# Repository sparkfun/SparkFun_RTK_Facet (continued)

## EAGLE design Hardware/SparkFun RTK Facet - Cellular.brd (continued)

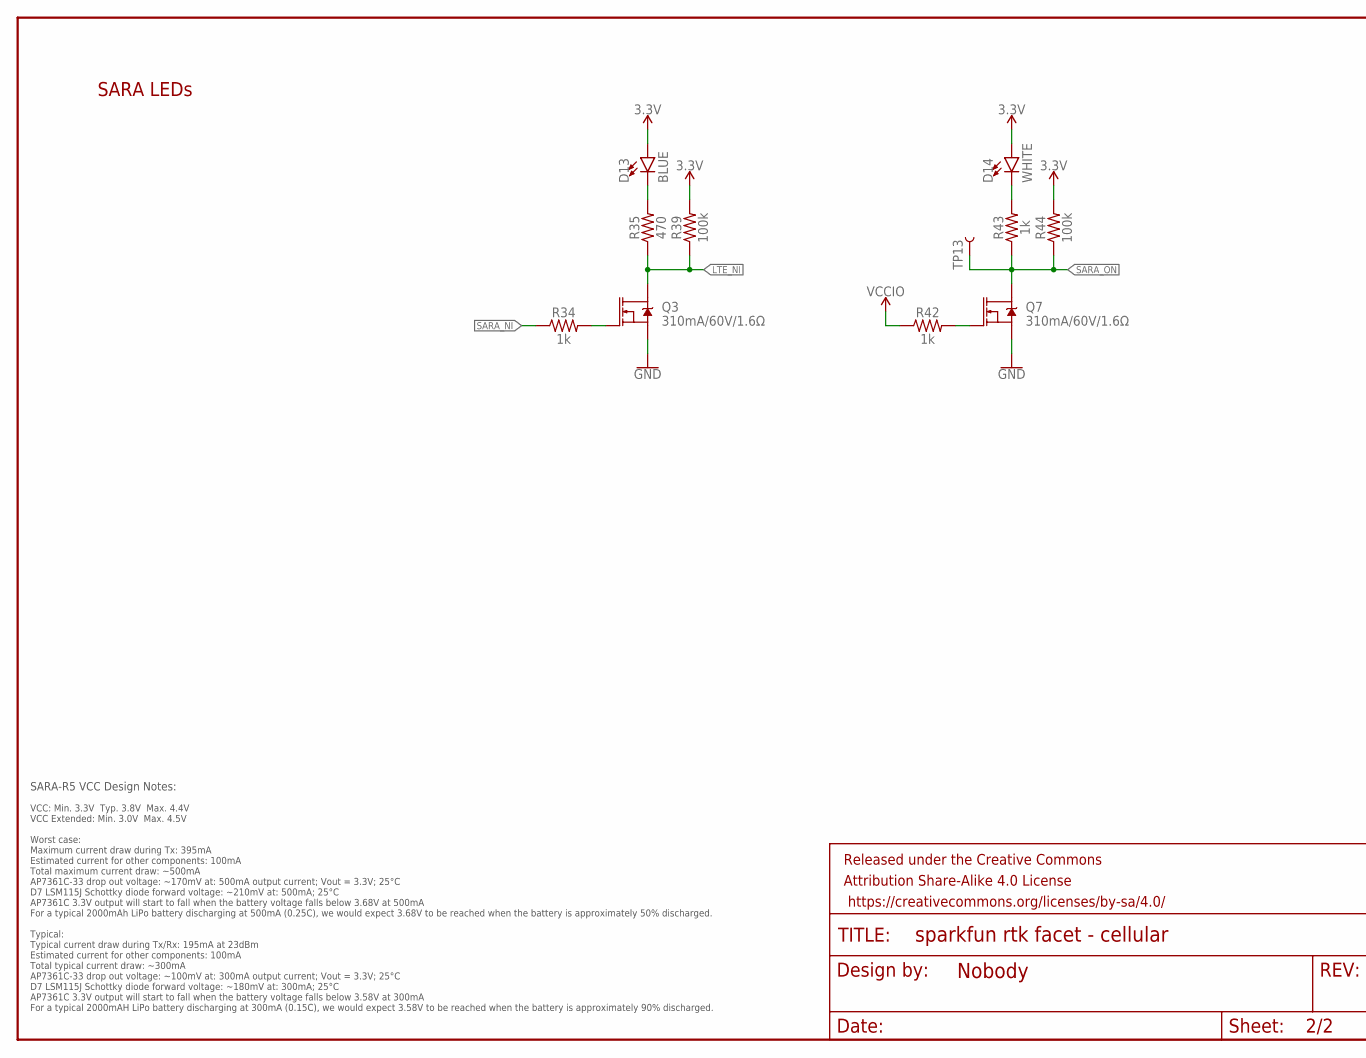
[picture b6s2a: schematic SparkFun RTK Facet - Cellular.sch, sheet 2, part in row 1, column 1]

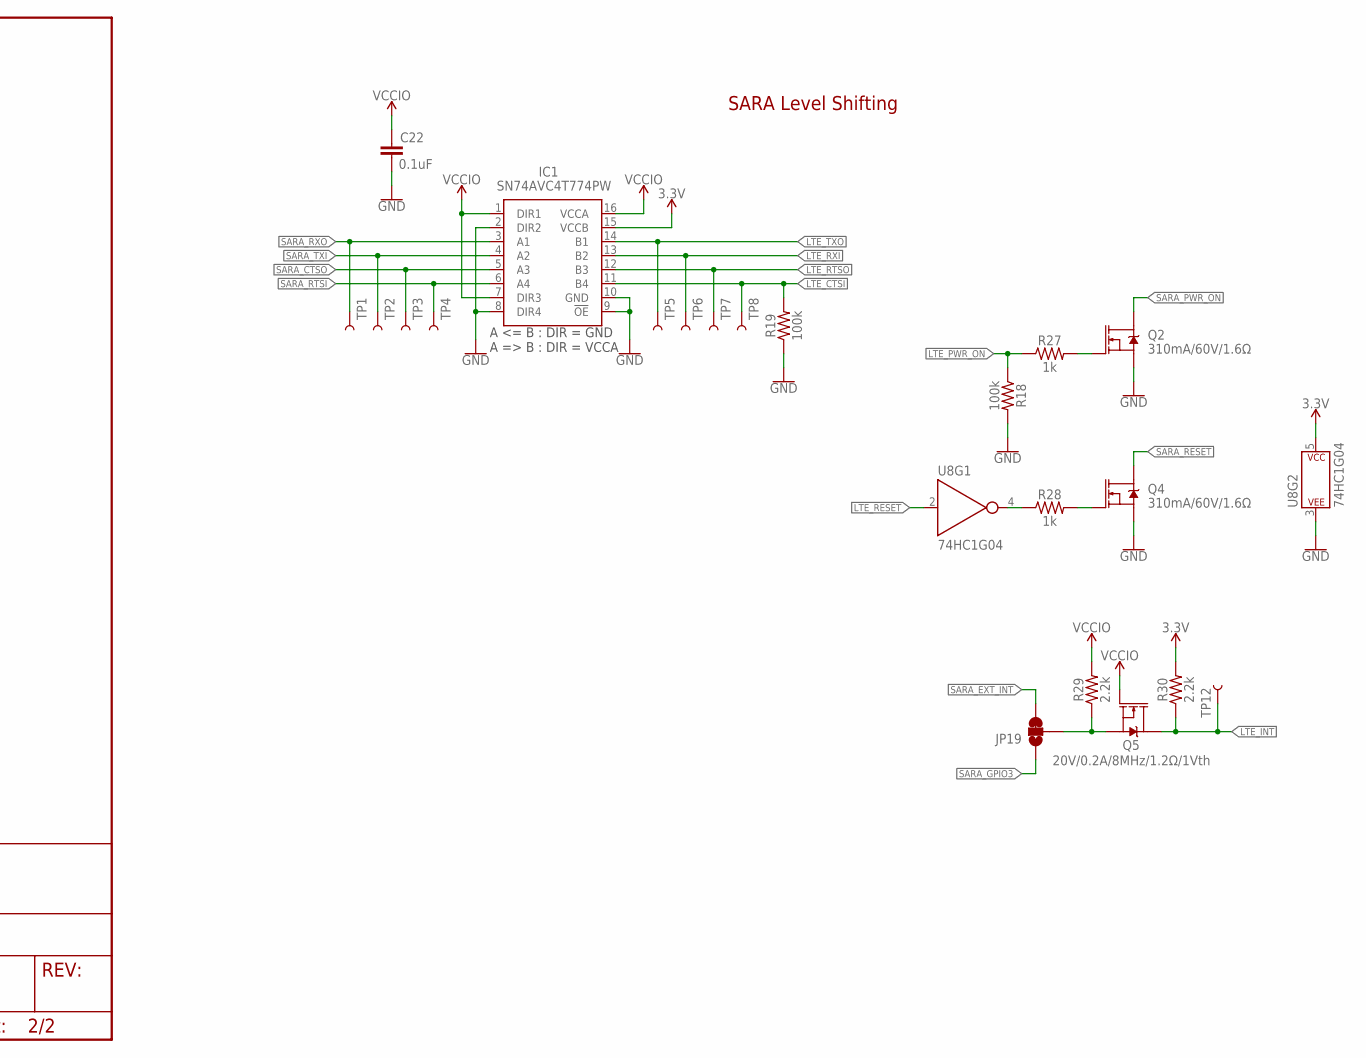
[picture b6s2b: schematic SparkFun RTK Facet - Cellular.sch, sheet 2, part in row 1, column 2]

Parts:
C22: 0.1uF; 0603
D13: BLUE; LED-0603
D14: WHITE; LED-0603
FRAME2: FRAME-LETTERNO_PACKAGE; DUMMY
IC1: SN74AVC4T774PW; SOP65P640X120-16N
JP19: JUMPER-SMT_3_1-NC_TRACE_SILK; SMT-JUMPER_3_1-NC_TRACE_SILK
Q2, Q3, Q4, Q7: 310mA/60V/1.6Ω; SOT323
Q5: 20V/0.2A/8MHz/1.2Ω/1Vth; SOT-416FL
R18, R19, R39, R44: 100k; 0603
R27, R28, R34, R42, R43: 1k; 0603
R29, R30: 2.2k; 0603
R35: 470; 0603
TP1, TP2, TP3, TP4, TP5, TP6, TP7, TP8, TP12, TP13: TEST-POINT3; PAD.03X.03
U8: 74HC1G04; SOT353

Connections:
3.3V: D13.A, D14.A, IC1.15 (VCCB), R30.2, R39.2, R44.2, U8.5 (P$V+); also elsewhere on the board
GND: C22.2, IC1.2 (DIR2), IC1.8 (DIR4), IC1.9 (!OE), IC1.10 (GND), Q2.2 (S), Q3.2 (S), Q4.2 (S), Q7.2 (S), R18.2, R19.1, U8.3 (P$V-); also elsewhere on the board
LTE_!RESET!: U8.2 (A); also elsewhere on the board
LTE_CTSI: IC1.11 (B4), R19.2, TP8.P$1; also elsewhere on the board
LTE_INT: Q5.3 (D), R30.1, TP12.P$1; also elsewhere on the board
LTE_NI: Q3.3 (D), R35.1, R39.1; also elsewhere on the board
LTE_PWR_ON: R18.1, R27.1; also elsewhere on the board
LTE_RTSO: IC1.12 (B3), TP7.P$1; also elsewhere on the board
LTE_RXI: IC1.13 (B2), TP6.P$1; also elsewhere on the board
LTE_TXO: IC1.14 (B1), TP5.P$1; also elsewhere on the board
unnamed: Q2.1 (G), R27.2
unnamed: Q4.1 (G), R28.2
unnamed: R28.1, U8.4 (Y)
unnamed: Q3.1 (G), R34.2
unnamed: D13.C, R35.2
unnamed: JP19.2, Q5.2 (S), R29.1
unnamed: Q7.1 (G), R42.2
unnamed: D14.C, R43.2
SARA_!ON!: Q7.3 (D), R43.1, R44.1, TP13.P$1
SARA_!RESET!: Q4.3 (D); also elsewhere on the board
SARA_CTSO: IC1.5 (A3), TP3.P$1; also elsewhere on the board
SARA_EXT_INT: JP19.3; also elsewhere on the board
SARA_GPIO3: JP19.1
SARA_NI: R34.1; also elsewhere on the board
SARA_PWR_ON: Q2.3 (D); also elsewhere on the board
SARA_RTSI: IC1.6 (A4), TP4.P$1; also elsewhere on the board
SARA_RXO: IC1.3 (A1), TP1.P$1; also elsewhere on the board
SARA_TXI: IC1.4 (A2), TP2.P$1; also elsewhere on the board
VCCIO: C22.1, IC1.1 (DIR1), IC1.7 (DIR3), IC1.16 (VCCA), Q5.1 (G), R29.2, R42.1; also elsewhere on the board

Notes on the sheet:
SARA Level Shifting
SARA LEDs
SARA-R5 VCC Design Notes:
VCC: Min. 3.3V Typ. 3.8V Max. 4.4V VCC Extended: Min. 3.0V Max. 4.5V Worst case: Maximum current draw during Tx: 395mA Estimated current for other components: 100mA Total maximum current draw: ~500mA AP7361C-33 drop out voltage: ~170mV at: 500mA output current; Vout = 3.3V; 25°C D7 LSM115J Schottky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

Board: 2 copper layers, 69 parts (4 on the bottom side), 40 nets, no tracks yet.

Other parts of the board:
U$2: CELLULAR1
U$13: CELLULAR0
U$14: RTK_FACET0
U$130: NANO0
U$131: SIM0

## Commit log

2021-02-05 Add 22ohm to USB hub D+/D-.
2021-02-11 Fix errors on all 3 boards after enclosure review.
    * Flip connector board completely. Mirror connectors.
    * Mirror connector on SD board
    * Move LED above SIM socket
    * Add membrane connector to SD board
    * Remove switch connector from main board
    * Increase width of connector board, 2mm on each side - 54mm wide
2021-02-11 Add ignore. Mvoe hardware files into sub directory.
2021-02-16 Move display connector to side so overlay connector can be center. Notch PCBs. Add dummy PCB height. Add dummy retention plate.
2021-02-16 Adjust top edges for alignment.
2021-02-22 Update PROD ID on 12 pin connector. Add gerbers for v10.
2021-02-22 Moved power LED to left side of front display.
2021-02-28 Update Retention Plate design as per current Fusion model
2021-05-13 Create retention plate
2021-05-13 Adding bits for overlay creation
2021-05-13 Removing duplicate retention plate.
2021-05-13 Adding retention plate
2021-05-13 Add prelim cellular design
2021-05-14 Move external connectors to button control. Add radio connector. Move ESP32 to VOUT. Move USB to VOUT. Remove USB from I2C.
2021-05-14 Net rename to indicate inputs vs outputs
2021-05-14 Add dimensions
2021-05-14 Move overlay connector further down. Invert overlay connector pins.
2021-05-14 Move into sub directories
2021-05-14 Increase height 2mm to 23. Move OLED connector up 1mm. Move overlay connector down.
2021-05-14 Update silk
2021-05-14 Change to NO jumper for I2C pullups
2021-05-14 Increase external connector board height to 23mm.
2021-05-14 Double up 3.3V on cell connector. Create dummy test board.
2021-05-14 Double up 3.3V rail on Radio connector.
2021-05-14 v11 External Connector Gerbers
2021-05-14 Add gerbers for v11 Display board
2021-05-14 Gerbers for v11 main board
2021-05-14 Add retention plate gerbers v10
2021-06-22 Add overlays
2021-06-22 Adding production panels.
2021-06-25 Change connector panel orientation.
2021-08-30 Change to push push socket on cellular board.
2021-08-30 Change to external pins SD socket on display board.
2021-08-30 Add production panel for Display v13 PCB.
2021-09-23 Add route out. Panel files for v11.
2021-09-23 Add impedance control note to mainboard
2021-10-01 Paul edits. Move dummy to sub-folder
2021-10-01 Add Buzzard text
2021-10-04 Add cellular board production files
2021-10-05 Add r2 labels (SMA fixes). Restructure folders.
2021-11-22 Reduce Main, Connector, Display, and Cell board widths by 1mm to allow for v-score protrusion.
2021-12-03 Add revisions to schematics. Add PDFs of schematics.
2021-12-03 Remove old files
2021-12-14 Add Mechanicals
    - Make Directory "Mechanical"
    - Add PDF Drawings
    - Add Fusion Archive
    - Add Meshes and Solid for all parts designed in house
2021-12-14 Rename readme.md to README.md
2021-12-15 Create README.md
    Initial ReadMe according to SFE Template guidelines
2021-12-15 Update readme. Add firmware note.
2021-12-20 Move thermistor from heat sources.
2021-12-20 Update ESP32 to larger FP.
2021-12-20 Adjust ESP32 FP.
2022-01-03 Add panel files for main v12, connector v12, display v14
2022-01-03 Update WiFi overlay
2022-02-03 Update issue templates
2022-02-24 Extend retention plate length to make it reversible. Add LTE only sticker.
2022-04-08 Add 915MHz label
2022-04-08 Move to LIF overlay connector.
2022-04-11 Change to LIF 6 pin connector, remove GND plane around accel.
2022-05-18 Add LBand stickers
2022-05-19 v15 panel files. Add tCream to LIF.
2022-05-19 Add tCream to LIF connector on display board v15
2022-05-19 Add IDs to schematic
2022-06-09 Add L-Band main board
2022-06-15 Add I2C addresses to schematics
2022-08-30 Add I2C test header to display board - v1.6
2023-06-22 Fix product manual link
2023-08-24 Sticker: Update Facet ARP
2023-08-24 Facet v13: change charger IC FP, discrete 33s, change cream on ESP32.
2023-08-24 Remove silk from around the accel FP for DFM.
2023-08-24 Remove R1, change charger FP, change 33 discretes, ESP32 DFM paste.
2023-08-25 Close jumpers between ZED/NEO. Change resistor IDs to indicate L-Band Direct.
2023-08-25 Add v14 panel
2023-09-01 Update ID resistors.
2023-09-01 Update ID resistors
2024-09-26 Convert connector and display boards to KiCad
2024-09-26 Fix part number on LIF
2024-10-02 Add route out text
2024-10-02 Add DRC exclusions
2024-10-02 Add PDF and ZIP
